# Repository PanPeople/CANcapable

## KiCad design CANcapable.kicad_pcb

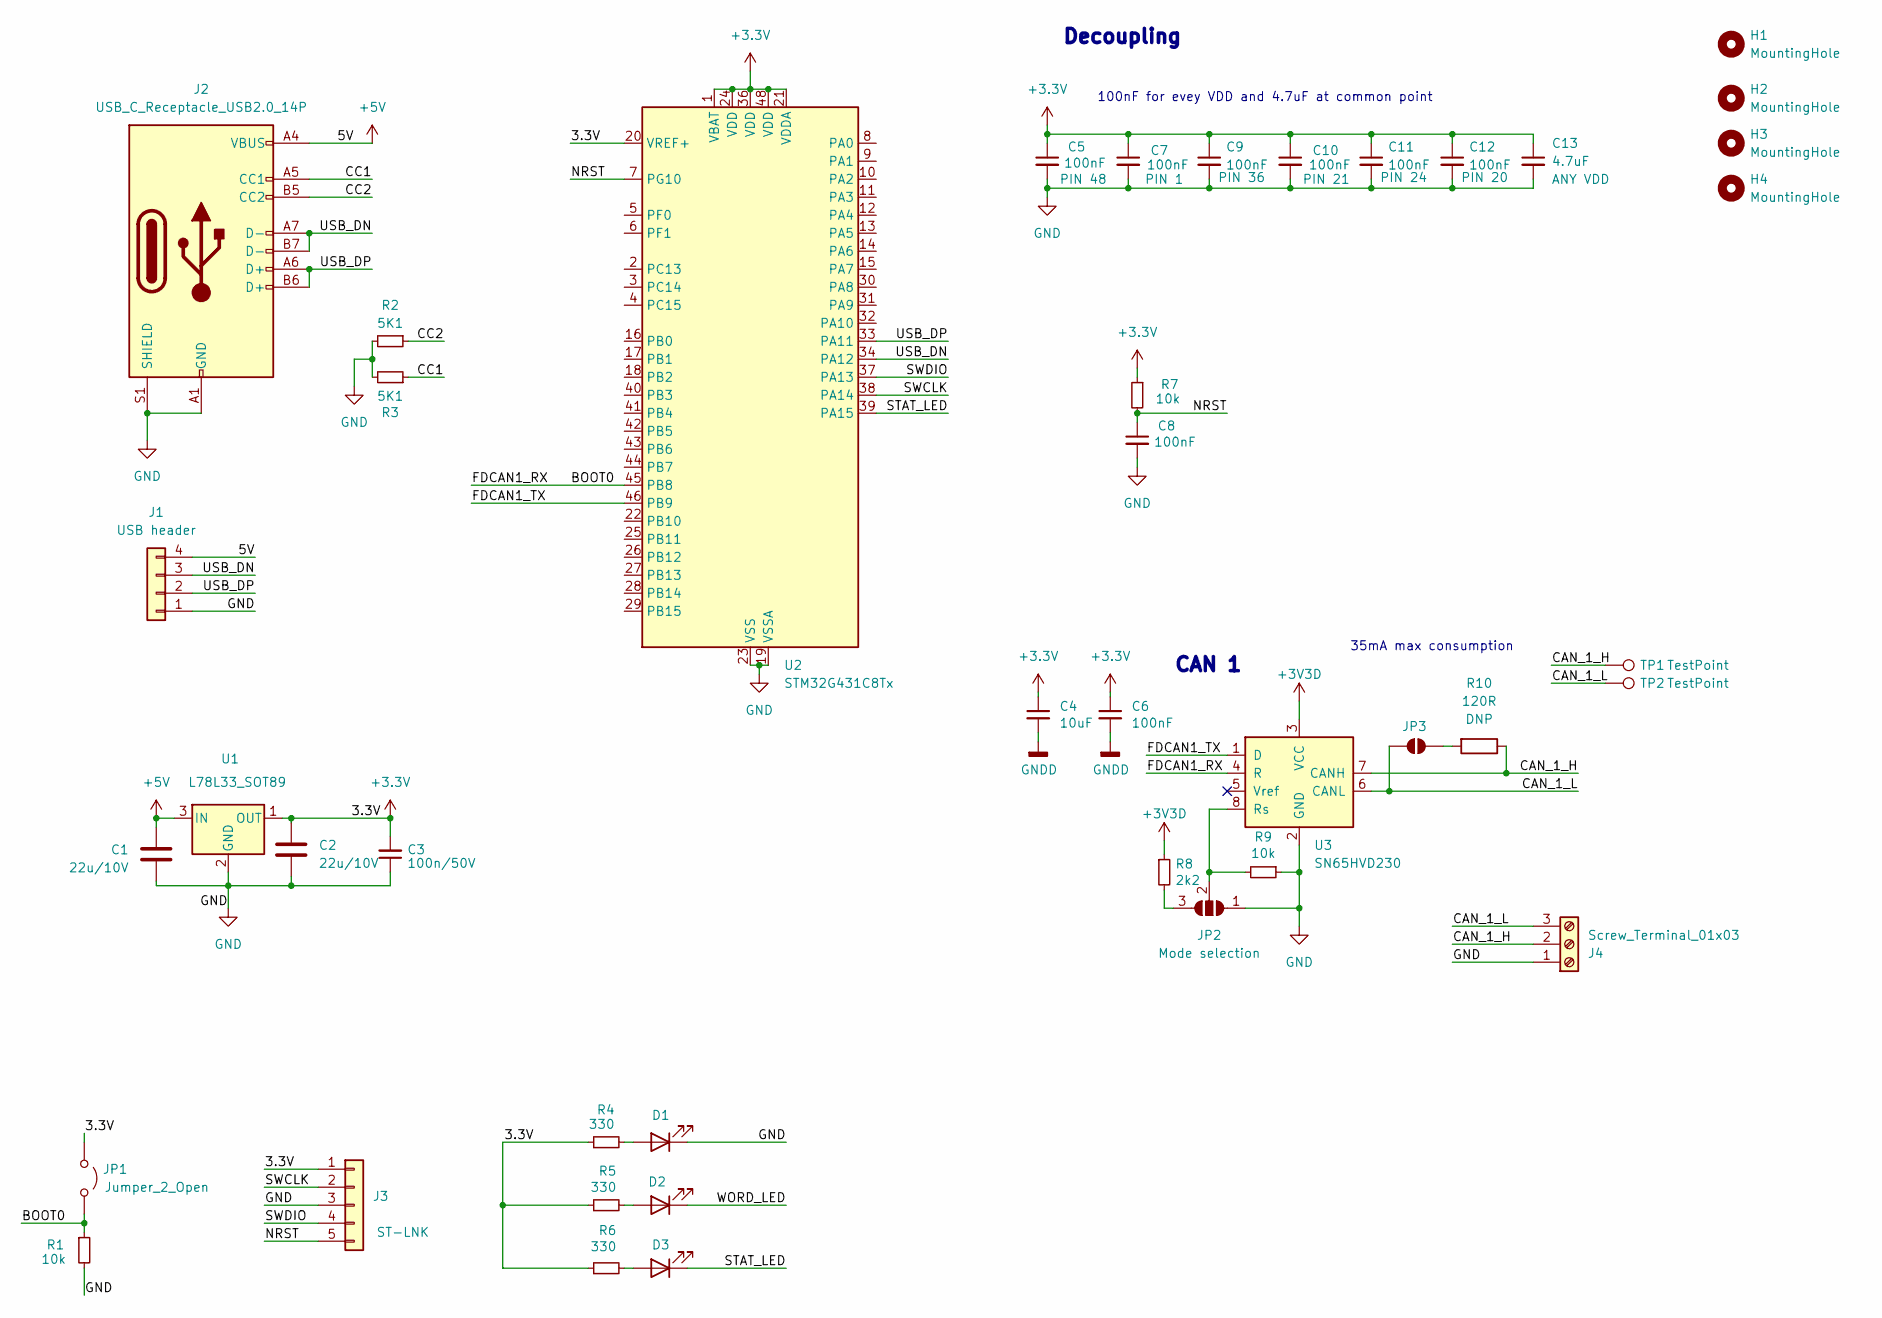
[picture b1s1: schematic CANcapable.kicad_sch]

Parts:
C1, C2: 22u/10V; C_0805_2012Metric_Pad1.18x1.45mm_HandSolder; MPN CL21X226MPYNNWE
C3: 100n/50V; C_0603_1608Metric_Pad1.08x0.95mm_HandSolder
C4: 10uF; C_0603_1608Metric_Pad1.08x0.95mm_HandSolder; MPN TMK212BBJ106KG-T
C5, C7, C8, C9, C10, C11, C12: 100nF; C_0603_1608Metric_Pad1.08x0.95mm_HandSolder; MPN CL10A475KP8NNNC
C6: 100nF; C_0603_1608Metric_Pad1.08x0.95mm_HandSolder; MPN CL10B104KB8NNND
C13: 4.7uF; C_0603_1608Metric_Pad1.08x0.95mm_HandSolder; MPN CL10A475KP8NNNC
D1, D2, D3: LED_0805_2012Metric_Pad1.15x1.40mm_HandSolder
H1, H2, H3, H4: MountingHole; MountingHole_3.2mm_M3_ISO7380_Pad
J1: USB header; PinHeader_1x04_P2.54mm_Vertical
J2: USB_C_Receptacle_USB2.0_14P; USB_C_Receptacle_HRO_TYPE-C-31-M-12
J3: Conn_01x05; PinHeader_1x05_P2.54mm_Vertical
J4: Screw_Terminal_01x03; TerminalBlock_MaiXu_MX126-5.0-03P_1x03_P5.00mm
JP1: Jumper_2_Open; PinHeader_1x02_P2.54mm_Vertical
JP2: SolderJumper_3_Open; SolderJumper-3_P1.3mm_Open_Pad1.0x1.5mm
JP3: SolderJumper_2_Open; PinHeader_1x02_P2.54mm_Vertical
R1, R7, R9: 10k; R_0603_1608Metric_Pad0.98x0.95mm_HandSolder; MPN WF06P-10K-5%
R2, R3: 5K1; R_0603_1608Metric_Pad0.98x0.95mm_HandSolder; MPN WF06P-10K-5%
R4, R5, R6: 330; R_0603_1608Metric_Pad0.98x0.95mm_HandSolder
R8: 2k2; R_0603_1608Metric_Pad0.98x0.95mm_HandSolder; MPN AC0603JR-072K2L
R10: 120R; R_0805_2012Metric_Pad1.20x1.40mm_HandSolder; MPN SMD0805-120R-1%
TP1, TP2: TestPoint; TestPoint_Pad_1.0x1.0mm
U1: L78L33_SOT89; SOT-89-3_Handsoldering
U2: STM32G431C8Tx; LQFP-48_7x7mm_P0.5mm
U3: SN65HVD230; SOIC-8_3.9x4.9mm_P1.27mm; MPN SN65HVD230DG4

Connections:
+3.3V: C2.1, C3.2, C4.1, C5.1, C6.1, C7.1, C9.1, C10.1, C11.1, C12.1, C13.1, J3.1, JP1.1 (A), R4.1, R5.1, R6.1, R7.1, U1.1 (OUT), U2.1 (VBAT), U2.20 (VREF+), U2.21 (VDDA), U2.24 (VDD), U2.36 (VDD), U2.48 (VDD)
+3V3D: R8.1, U3.3 (VCC)
+5V: C1.1, J1.4, J2.A4 (VBUS), J2.A9 (VBUS), J2.B4 (VBUS), J2.B9 (VBUS), U1.3 (IN)
/BOOT0: JP1.2 (B), R1.1, U2.45 (PB8), U3.4 (R)
/CAN_1_H: J4.2, R10.1, TP1.1, U3.7 (CANH)
/CAN_1_L: J4.3, JP3.1 (A), TP2.1, U3.6 (CANL)
/CC1: J2.A5 (CC1), R3.1
/CC2: J2.B5 (CC2), R2.1
/FDCAN1_TX: U2.46 (PB9), U3.1 (D)
/NRST: C8.1, J3.5, R7.2, U2.7 (PG10)
/STAT_LED: D3.1 (K), U2.39 (PA15)
/SWCLK: J3.2, U2.38 (PA14)
/SWDIO: J3.4, U2.37 (PA13)
/USB_DN: J1.3, J2.A7 (D-), J2.B7 (D-), U2.34 (PA12)
/USB_DP: J1.2, J2.A6 (D+), J2.B6 (D+), U2.33 (PA11)
/WORD_LED: D2.1 (K)
GND: C1.2, C2.2, C3.1, C5.2, C7.2, C8.2, C9.2, C10.2, C11.2, C12.2, C13.2, D1.1 (K), J1.1, J2.A1 (GND), J2.A12 (GND), J2.B1 (GND), J2.B12 (GND), J2.S1 (SHIELD), J3.3, J4.1, JP2.1 (A), R1.2, R2.2, R3.2, R9.1, U1.2 (GND), U2.19 (VSSA), U2.23 (VSS), U2.35 (VSS), U2.47 (VSS), U3.2 (GND)
GNDD: C4.2, C6.2
unnamed: D1.2 (A), R4.2
unnamed: D2.2 (A), R5.2
unnamed: D3.2 (A), R6.2
unnamed: JP2.3 (B), R8.2
unnamed: JP2.2 (C), R9.2, U3.8 (Rs)
unnamed: JP3.2 (B), R10.2

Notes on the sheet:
100nF for evey VDD and 4.7uF at common point
Decoupling
CAN 1
35mA max consumption

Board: 2 copper layers, 42 parts (0 on the bottom side), 23 nets, no tracks yet.

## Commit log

2025-04-16 components list complete
2025-04-16 added missing symbols
2025-04-17 begin layout
